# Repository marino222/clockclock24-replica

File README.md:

# ClockClock 24 Replica

This project is a hardware and software replica of the kinetic art piece "ClockClock 24" by *Humans Since 1982*, inspired by and building upon the work of [Vallasc](https://github.com/Vallasc/clockclock24-replica) with several hardware modifications and improvements. The clock features 24 double-shaft stepper motors arranged in an 8x3 matrix, with motors grouped in sets of three on custom PCBs, of which there are eight in total. Each board is controlled by a Raspberry Pi Pico microcontroller acting as a slave, while all slave boards communicate with a central ESP32 master via the I2C protocol. The ESP32 also provides a web interface for remote control and configuration.

---

## Table of Contents

1. [Repository Structure](#repository-structure)
2. [Hardware](#hardware)
    1. [Electronics](#electronics)
        1. [Motors](#motors)
        2. [Motor Drivers](#motor-drivers)
        3. [Microcontrollers](#microcontrollers)
        4. [PCB](#pcbs)
        5. [Power Supply](#power-supply)
    2. [Mechanics](#mechanics)
        1. [Clock hands](#clock-hands)
        2. [Fixation brackets](#fixation-brackets)
        3. [Front panel](#front-panel)
    3. [BOM](#bom)
3. [Software](#software)
    1. [Master](#master)
    2. [Slave](#slave)
    3. [Web Interface](#web-interface)
4. [Credits](#credits)

---

## Repository Structure

```
ClockClock 24 Replica/
├── 3D files/
│   ├── final/
│   └── test/
├── docs/
│   ├── datasheets/
│   └── images/
├── firmware/
│   ├── arduino/
│   │   ├── AdvancedBoardTest/
│   │   ├── BoardTest/
|   |   ├── SerialBoardTest/
│   │   └── SpeedoDriveTest/
│   ├── platformio/
│   │   ├── master/
│   │   └── slave/
│   └── README.md
├── pcb/
│   ├── Clock PCB/
│   └── Motor Driver/
└── README.md
```

---

## Hardware

### Electronics

#### Motors
To drive the clock hands, the BKA30D-R5 (equivalent to VID28-05) stepper motors were chosen. They have a total of 4 coils, allowing for two concentric drive shafts which makes them perfect for this application. These motors were originally designed for dashboard applications in the automotive industry. There are a number of other options with concentric shafts, but this one seemed to be most suitable as other similar projects also used it. Furthermore, it is cheaply available (around 4$ on Aliexpress) and draws little current.

<p align="center">
    
    <br><em>BKA30D-R5 stepper motor</em>
</p>

The BKA30D-R5 allows for microstepping up to 1/12 degrees per microstep, which is ideal to achieve smooth movement of the clock hands. See datasheet for more details: [BKA30D-R5 Datasheet](docs/datasheets/BKA30D-xx_datasheet.pdf).

*Note: As standard, this motor comes with mechanical endstops. On Aliexpress there are some vendors that sell it without endstops, otherwise you will need to cut off the endstops yourself.*

---

#### Motor Drivers
The steppers could in theory be driven directly from the microcontroller. However, the GPIO pins are limited and it is usually best practice to use a dedicated motor driver. For this reason, the VID6606 motor driver was chosen. It is specifically designed for the BKA30D-R5 (VID28-05) motor. One VID6606 can drive 4 motors (8 coils) in total. Per motor, it only needs two inputs: `f(SCX)` and `DIR`. As standard, this controller has built-in microstepping, which means with each rising edge of the SCX input the motor will perform one microstep in the direction specified by the DIR input.

The [VID6606 Datasheet](docs/datasheets/VID6606_datasheet.pdf) specifically recommends the use of smoothing capacitors to reduce electrical noise. Therefore, this [Motor-Controller-PCB from Hackaday](https://hackaday.io/project/187630-stepper-driver-for-dashpanel-instruments) was used. I didn't make any changes to it because it was already tested by [doctek](https://hackaday.io/doctek). Thus, it is designed to be used as a breakout board on the custom Clock PCB.

<p align="center"><em>Rendered image of the motor driver PCB</em></p>

During testing, the steppers were quite noisy. I first suspected the motor drivers and tried some alternatives (DRV8834, TMC2208), but that didn't help much, so I stayed with the VID6606. 

The real cause turned out to be mechanical play in the motor shafts. I also noticed the noise only appears at certain speeds, at full speed it mostly goes away. So adjusting the acceleration profile in software might help. For now I decided to leave the mechanical play as-is, since adding a bearing would be quite complex.

---

#### Microcontrollers
An ESP32 was chosen to run the master code, while multiple Raspberry Pi Picos are used as slave controllers. The ESP32 sends all the commands via I2C protocol to the slave boards. The main reason for this choice is that almost the same controllers were used in the reference project ([Vallasc/clockclock24-replica](https://github.com/Vallasc/clockclock24-replica)). Since I want to copy the software as closely as possible, I stuck with the same controllers. They are also widely available for a reasonable price and are easy to work with.

<p align="center"><em>Raspberry Pi Pico (left) and ESP32 (right)</em></p>

---

#### PCB
For the project, a custom Clock PCB was designed to hold three BKA30D-R5 motors, which is the maximum number of motors that can be driven by one Raspberry Pi Pico regarding available GPIO pins. In total, there are eight of these PCBs, resulting in an 8x3 matrix of 24 motors. Each Clock PCB has two VID6606 motor driver breakout boards, of which one output is unused.

As a design choice, the PCB uses header pins to connect the motor drivers and the microcontroller. This makes it easy to replace components in case they break. While testing, this happened multiple times. Since the motor controllers were directly soldered onto the PCB in the beginning, I ended up throwing away the whole PCB each time a motor driver broke. The header pins solve this problem. As a bonus, the Picos can be switched out easily. This proved useful to quickly run a test program by replacing the "normal" slave controller with a test controller running different firmware.

<p align="center"><em>Rendered image of the Clock PCB. See PCB directory for more info</em></p>

<p align="center"><em>Assembled Clock PCB</em></p>

---

#### Power Supply
All the PCBs are connected by a JST-XH 4-pin connector in a daisy chain. Two wires are used for power (5V and ground) and two wires are used for I2C communication (SDA and SCL). In theory, it should be possible to power all eight PCBs from one Raspberry Pi Pico connected to a power supply via USB-C. However, in reality this didnt work (see below).

#### Power Consumption Table

| Device                | Normal Current (mA) | Peak Current (mA) | Quantity | Total Normal (mA) | Total Peak (mA) |
|-----------------------|---------------------|-------------------|----------|-------------------|-----------------|
| Raspberry Pi Pico     | 50                  | 100               | 8        | 400               | 800             |
| Stepper Motor         | 20                  | 20                | 24       | 480               | 480             |
| ESP32                 | 260                 | 700               | 1        | 260               | 700             |
| **Total**             |                     |                   |          | **1140**          | **1980**        |

This table shows the estimated current draw for each device during normal use and at peak. The totals are for 8 Raspberry Pi Picos, 24 stepper motors, and 1 ESP32.

A Raspberry Pi Pico can provide up to 2 A via the VBUS pin when powered over USB-C, which should be enough even at peak load.

In practice I ran into power problems. When all motors start up at the same time, they draw a lot of current and the Pico's supply couldn't keep up, causing the ESP32 or some Picos to randomly shut down. To fix this, each PCB has an extra 2-pin JST power input. I disconnected the +5V lines on the JST-XH 4-pin connectors (GND and I2C stay connected) and wired the 2-pin terminals with 18 AWG wire and WAGO clamps to a separate supply.

The worst-case current draw is around 4 A, so I chose a 5 V / 6 A (30 W) PSU from [Amazon](https://www.amazon.de/dp/B0FY6691ZL), which gives a 2 A safety margin. It connects via a standard barrel jack that came with the PSU.

<p align="center"><em>Image of the connected PCBs</em></p>

### Mechanics

All mechanical parts are modeled in CAD. See the [3D files README](3D%20files/README.md) for the full assembly and a list of all printable parts.

#### Wooden Frame & Front panel

For the front panel I wanted a clean matte white look. After exploring several options (PVC, painted MDF, Corian), I found [expresszuschnitt.de](https://expresszuschnitt.de/) where you can order custom laser-cut materials. I ordered some samples and went with matte white acrylic (PERSPEX® Frost). The quality is excellent and the finish looks great. The front panel is bonded to the wooden frame with 3M VHB tape.

The frame itself is made from four wooden beams (see [BOM](#bom) for dimensions), connected at the corners by 3D-printed brackets that are screwed onto the beams.

<p align="center"><em>Wooden frame with acrylic front panel</em></p>

To give the clock a picture-frame look, I added medium oak ledges glued onto the main frame with mitered corners. Cutting accurate miters with basic tools was tricky, but after some sanding and oiling the result looks quite nice.

<p align="center"><em>Gluing the outer oak frame</em></p>

<p align="center"><em>Finished outer frame</em></p>

---

#### 2×3 Clock Arrays

The motors are grouped into 2×3 arrays. Each array consists of two PCBs connected by PCB mounts. Screw spacers raise the PCBs to the correct depth so the clock hands sit at the right position on the front. Everything is held together with M3 hex screws and threaded inserts.

<p align="center"><em>Exploded view (left) and front view (right) of a 2×3 clock array</em></p>

The arrays are aligned with the holes in the front panel using the [`mounting_aid.stl`](3D%20files/README.md) and then screwed to the wooden frame. The PSU barrel jack is clamped to the bottom of the frame with a 3D-printed bracket. A small cutout in the outer frame lets the power cable pass through.

<p align="center"><em>Clock arrays mounted to the frame</em></p>

---

#### Clamps

After mounting everything, I noticed a visible air gap between the 3D-printed PCB mounts and the front plate. This comes from slightly bent 3D-printed parts. The front panel also has quite a bit of flex.

<p align="center"><em>Gap between clock arrays and front panel</em></p>

To fix this, I designed a clamp to press the PCB holders onto the front plate. I tried different solutions, but none gave satisfying results. In the end, I settled on 3D-printed clamps that are screwed onto the main frame and use a spring section to press the PCB holders against the front plate.

<p align="center"><em>Section view of clamps</em></p>

Because of build-volume restrictions on my 3D printer, each clamp consists of multiple parts that are screwed together. As a result, and because the 3D-printed springs are quite strong, the clamp bends slightly. This can be seen in the image below. The bending causes the clamp to sit slightly higher than the outer frame. As a result, when the clock is mounted on a wall, the outer frame is not fully flush because the clamps push the clock outward. I decided to treat this as a design feature: it protects the rest of the clock, and the gap between the frame and the wall allows a bit of airflow, which helps cool the microcontrollers.

<p align="center"><em>Assembled clock with clamps</em></p>

---
### BOM

| Component | Description | Quantity | Source | Link |
|-----------|-------------|----------|--------|------|
| Clock PCB | Custom PCB holding 3 motors and a Raspberry Pi Pico. See PCB directory for the electronic BOM | 8 | JLCPCB, parts from AliExpress | [PCB README](pcb/Clock%20PCB/README.md) |
| PCB Mount (3D printed) | Mounts two PCBs together into one 2×3 array. 3 pieces per array | 9 | Self-printed | [3D files README](3D%20files/README.md) |
| PCB Mount Bottom (3D printed) | Same as PCB Mount but with corrected hole positions for the bottom PCB | 3 | Self-printed | [3D files README](3D%20files/README.md) |
| Mounting Bracket (3D printed) | Connects a 2×3 clock array to the wooden frame | 6 | Self-printed | [3D files README](3D%20files/README.md) |
| PSU Bracket (3D printed) | Clamps the PSU barrel jack to the wooden frame | 1 | Self-printed | [3D files README](3D%20files/README.md) |
| Frame Connector (3D printed) | Connects the outer frame corners. Parts are mirrored for each corner | 4 | Self-printed | [3D files README](3D%20files/README.md) |
| Screw Spacer (3D printed) | Raises PCBs slightly off the mounting brackets | 80 | Self-printed | [3D files README](3D%20files/README.md) |
| Lower Hand (3D printed) | Hour clock hand | 24 | Self-printed | [3D files README](3D%20files/README.md) |
| Upper Hand (3D printed) | Minute clock hand | 24 | Self-printed | [3D files README](3D%20files/README.md) |
| Wall Mount (3D printed) | Wall mounting part | 2 | Self-printed | [3D files README](3D%20files/README.md) |
| Outer Clamp (3D printed) | Outer clamp part | 5 | Self-printed | [3D files README](3D%20files/README.md) |
| Middle Clamp (3D printed) | Middle clamp part | 3 | Self-printed | [3D files README](3D%20files/README.md) |
| Y-Clamp (3D printed) | Y-clamp part | 1 | Self-printed | [3D files README](3D%20files/README.md) |
| Leaf Spring (3D printed) | Spring element used in the clamp assembly | 9 | Self-printed | [3D files README](3D%20files/README.md) |
| Edge Clamp (3D printed) | Edge clamp part for the right and left sides | 2 | Self-printed | [3D files README](3D%20files/README.md) |
| ESP32 mount (3D printed) | Mounting part for the ESP32 microcontroller | 1 | Self-printed | [3D files README](3D%20files/README.md) |
| Acrylic Front Panel | PERSPEX® Frost matte white acrylic, 900×400×5 mm | 1 | Imported from Germany | [expresszuschnitt.de](https://expresszuschnitt.de/) |
| Main Frame Long | 20×45×900 mm wood beam | 2 | Hardware store | [Jumbo](https://www.jumbo.ch/de/bauen-renovieren/holz/leisten-staebe/rechteckleisten/oecoplan-dachlatte-gehobelt-20-x-45mm--1m/p/4974449) |
| Main Frame Short | 20×45×400 mm wood beam | 2 | Hardware store | [Jumbo](https://www.jumbo.ch/de/bauen-renovieren/holz/leisten-staebe/rechteckleisten/oecoplan-dachlatte-gehobelt-20-x-45mm--1m/p/4974449) |
| Outer Frame Long | 8×40×920 mm oak ledge | 2 | Hardware store | [Jumbo](https://www.jumbo.ch/de/bauen-renovieren/holz/leisten-staebe/rechteckleisten/rechteckleiste-eiche-8x40-mm-1-m/p/4974225) |
| Outer Frame Short | 8×40×420 mm oak ledge | 2 | Hardware store | [Jumbo](https://www.jumbo.ch/de/bauen-renovieren/holz/leisten-staebe/rechteckleisten/rechteckleiste-eiche-8x40-mm-1-m/p/4974225) |
| Power Supply | 5 V / 6 A (30 W) PSU | 1 | Amazon | [Amazon](https://www.amazon.de/dp/B0FY6691ZL) |
| Power Wire | 18 AWG | ~3 m | AliExpress | |
| WAGO Clamps | Model 221-413 (3-conductor) | 14 | AliExpress | |
| 3M VHB Tape | 19 mm width | ~1 m | Hardware store | [3M Switzerland](https://www.3mschweiz.ch/3M/de_CH/p/c/klebebander/b/vhb/) |
| Countersunk Wood Screw | 4×16 mm | 24 | Hardware store | [Jumbo](https://www.jumbo.ch/de/maschinen-werkstatt/kleineisenwaren/schrauben/holzschrauben/ayce-senkkopf-universalholzschraube--4--16-mm/p/6932501) |
| Hex Screw | M3×8 mm | 96 | AliExpress | |
| Threaded Insert | M3×4×4 mm (for 3D-printed parts) | 96 | AliExpress | |

---

## Software

### Master

The master firmware runs on an ESP32 microcontroller and acts as the central brain of the clock. Its main responsibilities include:

- **Time Synchronization**: Automatically connects to WiFi to retrieve the current time, ensuring the clock is always accurate and handles time zones and daylight saving time seamlessly.
- **Clock Logic**: Orchestrates the movements of all clock hands, deciding exactly what positions they need to be in to display the time or play animations.
- **Communication**: Sends synchronized instructions to all eight slave boards so the 24 motors move perfectly together.
- **Web Server**: Hosts a web interface that allows you to configure and control the clock from any device.

The master code is built using PlatformIO with the Arduino framework.

### Slave

The slave firmware runs on each of the eight Raspberry Pi Pico microcontrollers, with each board responsible for controlling three BKA30D-R5 stepper motors (six individual clock hands). Key features include:

- **I2C Communication**: Listens for commands from the ESP32 master via I2C protocol
- **Motor Control**: Uses the AccelStepper library to provide smooth, accelerated motor movements with precise positioning
- **Automatic Addressing**: Determines its I2C address automatically based on DIP switch configuration (see below)

Each slave board operates independently once it receives position commands from the master, managing the acceleration profiles and step timing for its three motors in parallel.

Each slave board (Raspberry Pi Pico) determines its I2C address automatically based on four DIP switch pins (ADDR_1 through ADDR_4) defined in [`board_config.h`](firmware/platformio/slave/include/board_config.h). The address is calculated in [`board.cpp`](firmware/platformio/slave/src/board.cpp) by reading the state of these pins, which use INPUT_PULLUP logic. When a DIP switch is ON (connected to ground), it represents a binary 1. When OFF (open/floating), it represents a binary 0.

The master controller sends commands to each board sequentially as seen in [`clock_manger.cpp`](firmware/platformio/master/src/clock_manger.cpp), where I2C address 15 corresponds to the rightmost board. The first address is 0x08, because in the I2C protocol 0x01 to 0x07 are reserved.

#### Board Address Configuration (Left to Right)

| I2C Address | Binary | DIP 1 | DIP 2 | DIP 3 | DIP 4|
|-------------------|-------------|--------|----------------|--------------|--------------|
| 8  | 1000 | 1 | 0 | 0 | 0 |
| 9  | 1001 | 1 | 0 | 0 | 1 |
| 10 | 1010 | 1 | 0 | 1 | 0 |
| 11 | 1011 | 1 | 0 | 1 | 1 |
| 12 | 1100 | 1 | 1 | 0 | 0 |
| 13 | 1101 | 1 | 1 | 0 | 1 |
| 14 | 1110 | 1 | 1 | 1 | 0 |
| 15 | 1111 | 1 | 1 | 1 | 1 |

### Web Interface

The web interface is hosted directly on the ESP32 and provides an intuitive control panel for the ClockClock 24. To access it, simply connect to the same WiFi network as the ESP32 and navigate to its IP address in your browser. 

The UI provides the following features:
- **Live Preview**: View a real-time digital representation of what the physical clock is currently displaying.
- **Mode & Animation Selection**: Easily switch between the normal time display, various choreographies, or run test animations.
- **Sleep Time Configuration**: Define specific days and hours when the clock should stop moving to save power and reduce noise.
- **Wireless Configuration**: Seamlessly switch between the clock's own Hotspot mode or connect it to your home WiFi network.
- **Firmware Update**: Perform Over-The-Air (OTA) firmware updates directly from your browser.

The web interface is built using standard HTML, CSS, and JavaScript. Because the ESP32 has limited storage, a custom Node.js script is used to compress the web files. Before building the firmware, running `npm run minimize` minifies the UI files and converts them into a single, optimized C++ header file, which is then flashed onto the microcontroller.

For more technical details about the firmware, see the [firmware README](firmware/README.md).

### Clock Modes

The clock can operate in three distinct modes, which can be selected via the web interface:
- **OFF**: All clock hands move to a resting position (pointing straight down) and remain stationary.
- **LAZY**: A minimalist mode where the clock hands take the shortest, most direct path to the new time every minute, without any complex choreographies.
- **ANIMATED**: Every minute, the clock performs a choreography before settling on the new time. You can choose a specific animation or use the **Cycle** mode.

#### Cycle Mode & Randomness
When the **Cycle** animation is selected, the clock rotates through the available choreographies instead of playing the same one every minute. You have two options for how it cycles:
- **SEQ (Sequential)**: Plays the animations in a fixed order, cycling to the next one every minute.
- **RAND (Random)**: Plays a "random" animation each minute. Interestingly, this randomness is deterministic and based on the current time (a hash of the current minute of the day). This means the clock will always play the exact same animation, as the Web Interface.

### Animations

| Description      | Animation |
| ----------- | ----------- |
| Chaos |  |
| Waves |  |
| Circle |  |
| Spiral |  |
| Loom |  |
| Star |  |

## Credits

### Design — Humans Since 1982

**ClockClock 24 is an original kinetic art piece created by [Humans Since 1982](https://www.humanssince1982.com/).** All design rights, intellectual property, and artistic authorship of the ClockClock concept belong exclusively to them. This project is a non-commercial personal replica built out of admiration for their work. I make no claim to the design, the concept, or any related intellectual property.u are considering a similar project, please be aware of this and respect their rights.

---

### Reference Implementation — Vallasc

The firmware and PCB design of this project are largely based on the work of [Vallasc](https://github.com/Vallasc/clockclock24-replica). His open-source replica served as the primary reference for the software architecture, I2C communication protocol, clock logic, and overall system design. Without his work this project would have taken significantly longer to build.

---

### Motor Driver PCB — doctek

The motor driver breakout board design is taken from the [Stepper Driver for Dashpanel Instruments](https://hackaday.io/project/187630-stepper-driver-for-dashpanel-instruments) project by [doctek](https://hackaday.io/doctek) on Hackaday.io. The board was used without modifications. The `SpeedoDriveTest.ino` test sketch is also taken from that project.

---

### This Project

This repository is released under the [GNU General Public License v3.0](LICENSE). You are free to use, modify, and distribute it under the same terms, but **the design concept of ClockClock 24 remains the exclusive property of Humans Since 1982** and this license does not grant any rights to it.

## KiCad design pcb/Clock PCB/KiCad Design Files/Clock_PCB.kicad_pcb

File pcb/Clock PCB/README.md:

# Clock PCB — Main Board for ClockClock 24 Replica

This folder contains the design files, manufacturing resources, and assembly instructions for the Clock PCB used in the ClockClock 24 Replica project. The Clock PCB hosts three stepper motors, a Raspberry Pi Pico microcontroller, and connectors for two Motor Driver modules.

---

## Folder Contents

- **KiCad Design Files:** Schematic and layout for the Clock PCB.
- **Manufacturing Folder:**
  - Gerber files (ZIP) for PCB fabrication

---

## Manufacturing

1. **PCB Fabrication:**
   - Order the PCB from [JLCPCB](https://jlcpcb.com/) or a similar service.
   - Upload the Gerber ZIP file from the `Manufacturing` folder during the order process.

3. **Manual Assembly:**
    - Solder all the components manually

---

## Bill of Materials (BOM)

This BOM lists only the components that need to be soldered onto the Clock PCB. The full BOM for the final assembly is provided in [the main project README](../../README.md).

| Quantity | Reference      | Value                 | Footprint | Description               |
|----------|----------------|-----------------------|-----------|---------------------------|
| 3        | M1, M2, M3     | BKA30D-R5             | -         | Stepper Motor             |
| 2        | J1, J2         | JST-PH-4pin           | P2.0mm    | 4-pin JST PH, 90° angle   |
| 2        | -              | 20 pin female         | P2.54mm   |  20 Pin socket            |
| 2        | -              | 6 pin female header   | P2.54mm   | 6 Pin socket              |
| 1        | -              | 5 pin female header   | P2.54mm   | 5 Pin socket              |
| 1        | -              | 8 pin female header   | P2.54mm   | 8Pin socket               |
| 1        | SW1            | 4 bit                 | P2.54mm   | 4-bit DIP switch          |
| 1        | J3 (optional)  | Power connector       | P5.08mm   | Optional power connector  |

---

## Images

### Assembled Clock PCB Example
<p align="center">
  
  <br><em>Assembled Clock PCB</em>
</p>

### PCB Schematics
<p align="center">
  
  <br><em>Clock PCB Schematic</em>
</p>

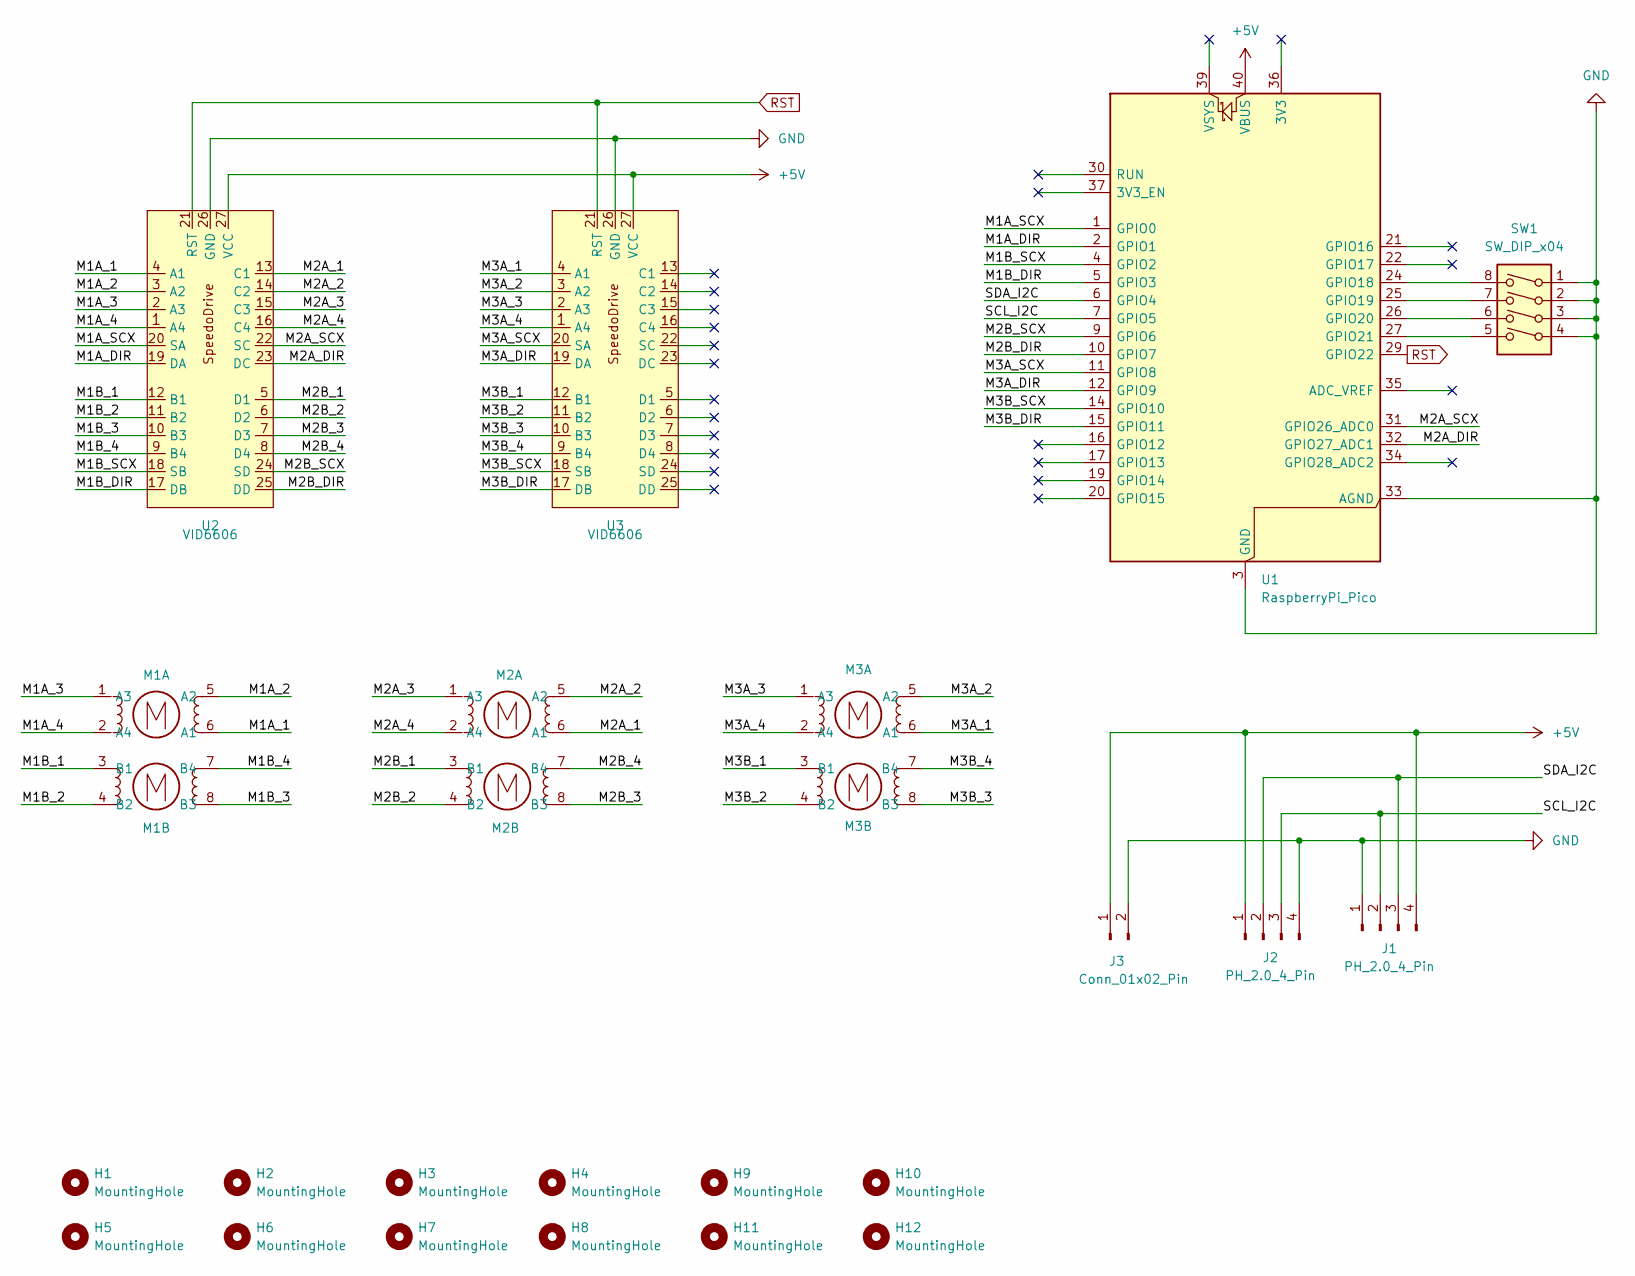
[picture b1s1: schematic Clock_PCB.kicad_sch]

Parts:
H1, H2, H3, H4, H5, H6, H7, H8, H9, H10, H11, H12: MountingHole; MountingHole_3.2mm_M3
J1, J2: PH_2.0_4_Pin; JST_PH_S4B-PH-K_1x04_P2.00mm_Horizontal
J3: Conn_01x02_Pin; TerminalBlock_Phoenix_MKDS-1,5-2-5.08_1x02_P5.08mm_Horizont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
M1, M2, M3: BKA30D-R5
SW1: SW_DIP_x04; SW_DIP_SPSTx04_Slide_9.78x12.34mm_W7.62mm_P2.54mm
U1: RaspberryPi_Pico; RaspberryPi_Pico_Common_THT_Header
U2, U3: VID6606; SpeedoDrive

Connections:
+5V: J1.4, J2.1, J3.1, U1.40 (VBUS), U2.27 (VCC), U3.27 (VCC)
/M1A_1: M1.6 (A1), U2.4 (A1)
/M1A_2: M1.5 (A2), U2.3 (A2)
/M1A_3: M1.1 (A3), U2.2 (A3)
/M1A_4: M1.2 (A4), U2.1 (A4)
/M1A_DIR: U1.2 (GPIO1), U2.19 (DA)
/M1A_SCX: U1.1 (GPIO0), U2.20 (SA)
/M1B_1: M1.3 (B1), U2.12 (B1)
/M1B_2: M1.4 (B2), U2.11 (B2)
/M1B_3: M1.8 (B3), U2.10 (B3)
/M1B_4: M1.7 (B4), U2.9 (B4)
/M1B_DIR: U1.5 (GPIO3), U2.17 (DB)
/M1B_SCX: U1.4 (GPIO2), U2.18 (SB)
/M2A_1: M2.6 (A1), U2.13 (C1)
/M2A_2: M2.5 (A2), U2.14 (C2)
/M2A_3: M2.1 (A3), U2.15 (C3)
/M2A_4: M2.2 (A4), U2.16 (C4)
/M2A_DIR: U1.32 (GPIO27_ADC1), U2.23 (DC)
/M2A_SCX: U1.31 (GPIO26_ADC0), U2.22 (SC)
/M2B_1: M2.3 (B1), U2.5 (D1)
/M2B_2: M2.4 (B2), U2.6 (D2)
/M2B_3: M2.8 (B3), U2.7 (D3)
/M2B_4: M2.7 (B4), U2.8 (D4)
/M2B_DIR: U1.10 (GPIO7), U2.25 (DD)
/M2B_SCX: U1.9 (GPIO6), U2.24 (SD)
/M3A_1: M3.6 (A1), U3.4 (A1)
/M3A_2: M3.5 (A2), U3.3 (A2)
/M3A_3: M3.1 (A3), U3.2 (A3)
/M3A_4: M3.2 (A4), U3.1 (A4)
/M3A_DIR: U1.12 (GPIO9), U3.19 (DA)
/M3A_SCX: U1.11 (GPIO8), U3.20 (SA)
/M3B_1: M3.3 (B1), U3.12 (B1)
/M3B_2: M3.4 (B2), U3.11 (B2)
/M3B_3: M3.8 (B3), U3.10 (B3)
/M3B_4: M3.7 (B4), U3.9 (B4)
/M3B_DIR: U1.15 (GPIO11), U3.17 (DB)
/M3B_SCX: U1.14 (GPIO10), U3.18 (SB)
/SCL_I2C: J1.2, J2.3, U1.7 (GPIO5)
/SDA_I2C: J1.3, J2.2, U1.6 (GPIO4)
GND: J1.1, J2.4, J3.2, SW1.1, SW1.2, SW1.3, SW1.4, U1.3 (GND), U1.8 (GND), U1.13 (GND), U1.18 (GND), U1.23 (GND), U1.28 (GND), U1.33 (AGND), U1.38 (GND), U2.26 (GND), U3.26 (GND)
unnamed: SW1.8, U1.24 (GPIO18)
unnamed: SW1.7, U1.25 (GPIO19)
unnamed: SW1.6, U1.26 (GPIO20)
unnamed: SW1.5, U1.27 (GPIO21)
RST: U1.29 (GPIO22), U2.21 (RST), U3.21 (RST)

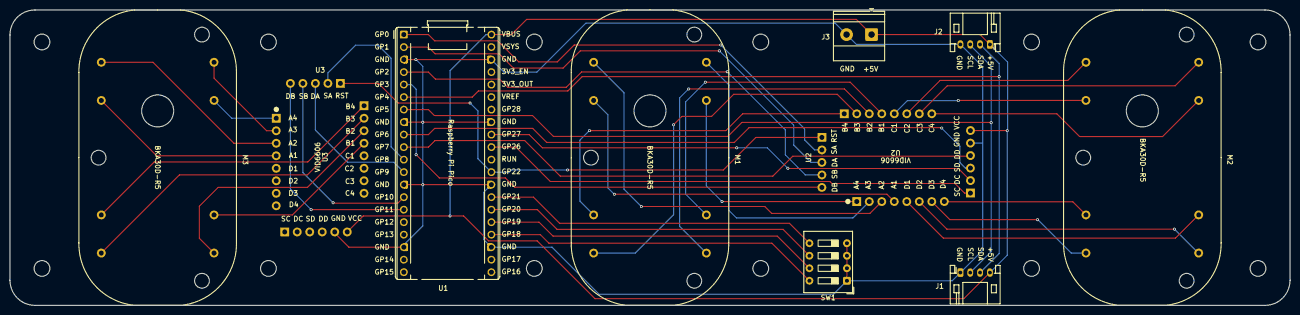
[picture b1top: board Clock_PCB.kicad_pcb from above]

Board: 2 copper layers, 260.0 x 60.0 mm, 22 parts (0 on the bottom side), 45 nets.

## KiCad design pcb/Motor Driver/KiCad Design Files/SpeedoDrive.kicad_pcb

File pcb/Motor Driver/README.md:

# Motor Driver PCB — VID6606 Breakout

This folder contains the design files, manufacturing resources, and assembly instructions for the Motor Driver PCB used in the ClockClock 24 Replica project. This board is a compact breakout for the VID6606 stepper driver IC, designed to be easily replaceable and compatible with the main Clock PCB.

---

## Folder Contents

- **KiCad Design Files:** Schematic and layout for the Motor Driver PCB.
- **Manufacturing Folder:**
  - Gerber files (ZIP) for PCB fabrication
  - [SpeedoDrive_BOM_SMD.csv](Manufacturing/SpeedoDrive_BOM_SMD.csv): Machine-readable BOM for SMD assembly

---

## Manufacturing 

1. **PCB Fabrication:**
   - The PCB was ordered from [JLCPCB](https://jlcpcb.com/)
   - Upload the Gerber ZIP file from the `Manufacturing` folder when placing your order

2. **SMD Assembly:**
    - The automatic assembly of SMD components (excluding the VID6606) was also ordered from JLCPCB.
    - During the order proces you will be prompted to upload a BOM file, to automatically populate the pcb. Use the CSV file in the `Manufacturing` folder for this purpose
    - Of course, the SMD Components can also be soldered manually if preferred.

3. **Manual Assembly:**
    - Since the VID6606 chip and the pin headers cannot be automatically assembled, these components must be soldered manually after receiving the PCB.

---

## Bill of Materials (BOM)

This BOM lists all components required to assemble one Motor Driver board.

| Quantity | Reference   | Value   | Footprint | Description           |
|----------|-------------|---------|-----------|-----------------------|
| 1        | U1          | VID6606 | —         | Stepper Driver IC     |
| 2        | C1, C6      | 6.8 µF  | 0805      | Ceramic Capacitor     |
| 2        | C2, C5      | 4.7 µF  | 0805      | Ceramic Capacitor     |
| 2        | C3, C4      | 100 nF  | 0603      | Ceramic Capacitor     |
| 9        | R1–R9       | 10 kΩ   | 0603      | Resistor              |
| 1        | J1          | Header 5P | 2.54 mm | Pin Header            |
| 1        | J2          | Header 8P | 2.54 mm | Pin Header            |
| 2        | J3, J4      | Header 6P | 2.54 mm | Pin Header            |

---

## Images

### Soldered PCB Example
Without Pin Headers
<p align="center">
  
  <br><em>Soldered Motor Driver PCB</em>
</p>

### PCB Schematics
<p align="center">
  
  <br><em>Motor Driver Schematic</em>
</p>

### Mechanical Pin Numbers
Below is an illustration of the mechanical pin numbers for the Speedo Drive PCB. This helps identify the physical pin layout and connections for assembly and troubleshooting. The pin numbering shown here was used to design the KiCad footprint for this board.

<p align="center">
  
  <br><em>Mechanical Pin Numbers for Speedo Drive PCB</em>
</p>

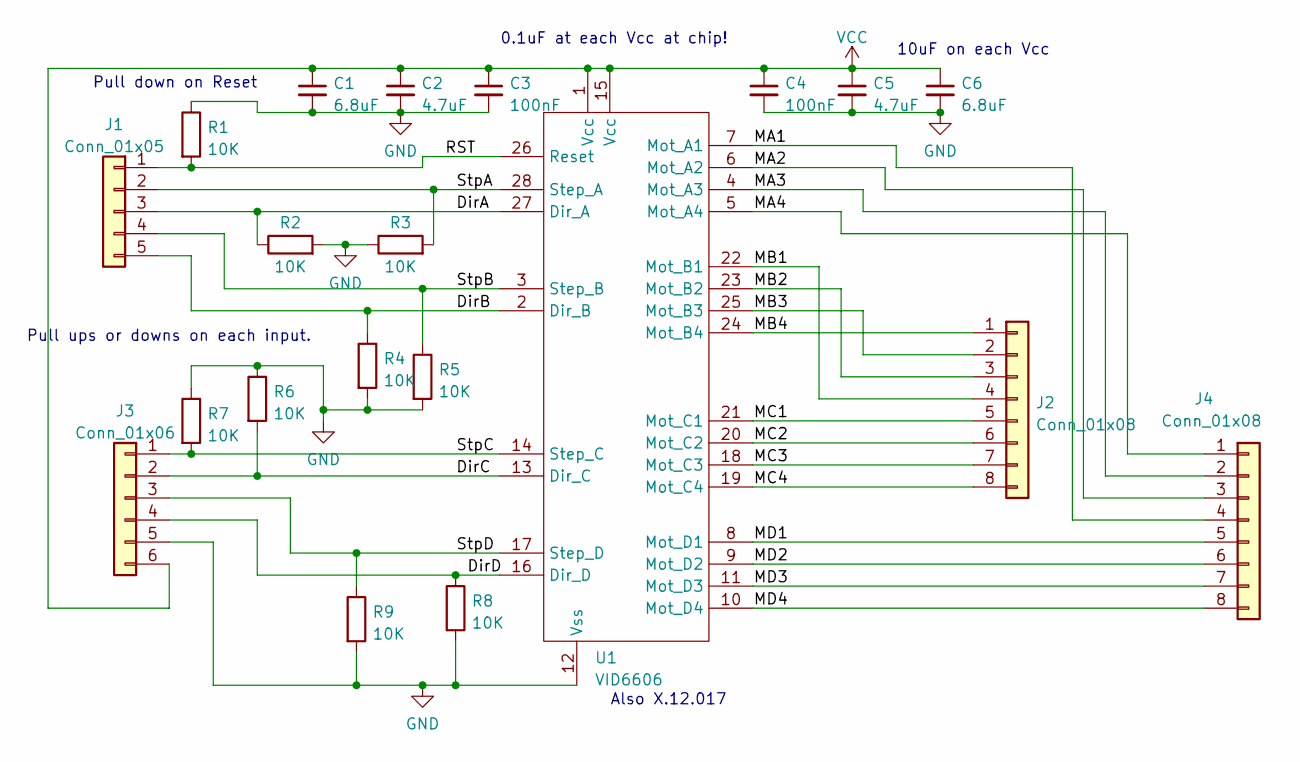
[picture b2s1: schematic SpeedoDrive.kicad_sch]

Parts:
C1, C6: 6.8uF; C_0805_2012MetricSQ; LCSC C5139488
C2, C5: 4.7uF; C_0805_2012MetricSQ; LCSC C1779
C3, C4: 100nF; C_0603_1608MetricSQ; LCSC C14663
J1: Conn_01x05; PinHeader_1x05_P2.54mm_Vertical
J2, J4: Conn_01x08; PinHeader_1x08_P2.54mm_Vertical
J3: Conn_01x06; PinHeader_1x06_P2.54mm_Vertical
R1, R2, R3, R4, R5, R6, R7, R8, R9: 10K; R_0603_1608MetricSQ; LCSC C25804
U1: VID6606; SOIC-28W_7.5x17.9mm_P1.27mm

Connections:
/DirA: J1.3, R2.1, U1.27 (Dir_A)
/DirB: J1.5, R4.1, U1.2 (Dir_B)
/DirC: J3.2, R6.2, U1.13 (Dir_C)
/DirD: J3.4, R8.1, U1.16 (Dir_D)
/MA1: J4.4, U1.7 (Mot_A1)
/MA2: J4.3, U1.6 (Mot_A2)
/MA3: J4.2, U1.4 (Mot_A3)
/MA4: J4.1, U1.5 (Mot_A4)
/MB1: J2.4, U1.22 (Mot_B1)
/MB2: J2.3, U1.23 (Mot_B2)
/MB3: J2.2, U1.25 (Mot_B3)
/MB4: J2.1, U1.24 (Mot_B4)
/MC1: J2.5, U1.21 (Mot_C1)
/MC2: J2.6, U1.20 (Mot_C2)
/MC3: J2.7, U1.18 (Mot_C3)
/MC4: J2.8, U1.19 (Mot_C4)
/MD1: J4.5, U1.8 (Mot_D1)
/MD2: J4.6, U1.9 (Mot_D2)
/MD3: J4.7, U1.11 (Mot_D3)
/MD4: J4.8, U1.10 (Mot_D4)
/RST: J1.1, R1.2, U1.26 (Reset)
/StpA: J1.2, R3.2, U1.28 (Step_A)
/StpB: J1.4, R5.1, U1.3 (Step_B)
/StpC: J3.1, R7.2, U1.14 (Step_C)
/StpD: J3.3, R9.1, U1.17 (Step_D)
GND: C1.2, C2.2, C3.2, C4.2, C5.2, C6.2, J3.5, R1.1, R2.2, R3.1, R4.2, R5.2, R6.1, R7.1, R8.2, R9.2, U1.12 (Vss)
VCC: C1.1, C2.1, C3.1, C4.1, C5.1, C6.1, J3.6, U1.1 (Vcc), U1.15 (Vcc)

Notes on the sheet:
0.1uF at each Vcc at chip!
Pull down on Reset
Also X.12.017
10uF on each Vcc
Pull ups or downs on each input.

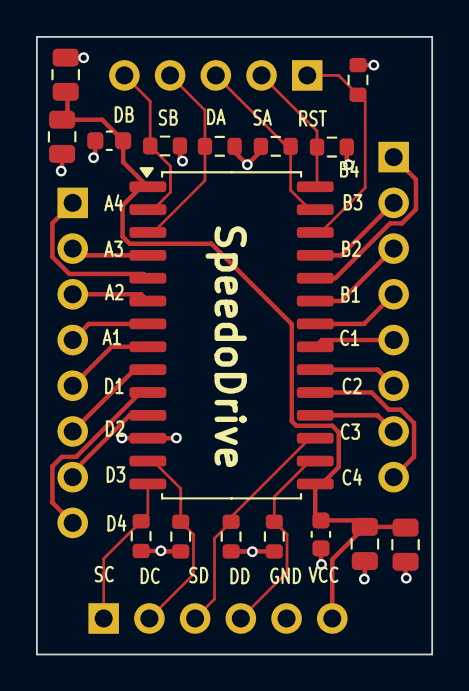
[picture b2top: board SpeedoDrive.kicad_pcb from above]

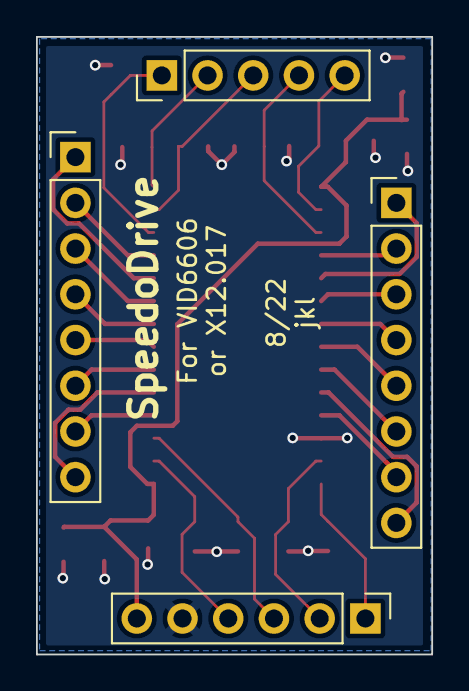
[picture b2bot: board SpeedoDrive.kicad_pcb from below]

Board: 2 copper layers, 22.0 x 34.3 mm, 20 parts (4 on the bottom side), 27 nets.

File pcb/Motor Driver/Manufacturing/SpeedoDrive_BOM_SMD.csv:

"Comment","Designator","Footprint","LCSC Part Number"
"6.8uF","C1,C6","0805","C5139488"
"4.7uF","C2,C5","0805","C1779"
"100nF","C3,C4","0603","C14663"
"10K","R1,R2,R3,R4,R5,R6,R7,R8,R9","0603","C25804"

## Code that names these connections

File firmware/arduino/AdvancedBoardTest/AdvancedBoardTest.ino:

/*
 * AdvancedBoardTest (ClockClock 24 Replica)
 *
 * Purpose
 * - Test any single stepper motor on the board by selecting it via a 4-bit DIP address (GPIO 18–21).
 * - While the address is valid and unchanged, the selected motor continuously:
 *     (1) rotates N full rotations forward
 *     (2) then rotates N full rotations backward
 *   repeating forever.
 * - If the address changes, the currently commanded motor is stopped (no further step pulses are issued)
 *   and control immediately switches to the newly addressed motor.
 * - If the address does not match any defined motor, all motors remain stopped.
 *
 * 4-bit address -> stepper mapping (exactly 6 unique addresses)
 * - Bit order: GPIO18 = b0 (LSB), GPIO19 = b1, GPIO20 = b2, GPIO21 = b3 (MSB)
 * - DIP read uses INPUT_PULLUP:
 *     switch ON (to GND)  => reads LOW  => bit = 1
 *     switch OFF (open)   => reads HIGH => bit = 0
 *
 *   Address (b1 b2 b3 b4)   Hex   Motor
 *   ---------------------   ---   -----
 *   0  0  0  0              0x0   A
 *   0  0  0  1              0x1   B
 *   0  0  1  0              0x2   C
 *   0  0  1  1              0x3   D
 *   0  1  0  0              0x4   E
 *   0  1  0  1              0x5   F
 *
 * GPIO usage summary
 * - Motor STEP/DIR pins:
 *     A: STEP=0  DIR=1
 *     B: STEP=2  DIR=7
 *     C: STEP=26 DIR=27
 *     D: STEP=6  DIR=3
 *     E: STEP=8  DIR=9
 *     F: STEP=10 DIR=11
 */

#include <Arduino.h>
#include <AccelStepper.h>

// Reuse the BoardTest notion of "one full rotation".
#define STEPS (360 * 12)

// Motion pattern constants
static const uint8_t N_ROTATIONS = 3;  // N (forward and backward); adjust as desired
static const long FORWARD_STEPS = (long)N_ROTATIONS * (long)STEPS;
static const long BACKWARD_STEPS = (long)N_ROTATIONS * (long)STEPS;

// DIP switch pins (4-bit binary address input)
static const uint8_t ADDR_B0_PIN = 18;
static const uint8_t ADDR_B1_PIN = 19;
static const uint8_t ADDR_B2_PIN = 20;
static const uint8_t ADDR_B3_PIN = 21;

#define A_STEP 0  // f(scx)
#define A_DIR 1   // CW/CCW
#define B_STEP 2  // f(scx)
#define B_DIR 7   // CW/CCW

#define C_STEP 26  // f(scx)
#define C_DIR 27   // CW/CCW
#define D_STEP 6   // f(scx)
#define D_DIR 3    // CW/CCW

#define E_STEP 8   // f(scx)
#define E_DIR 9    // CW/CCW
#define F_STEP 10  // f(scx)
#define F_DIR 11   // CW/CCW

#define RESET 22

// Stepper objects (exactly as in BoardTest.ino)
AccelStepper s_A(AccelStepper::DRIVER, A_STEP, A_DIR);
AccelStepper s_B(AccelStepper::DRIVER, B_STEP, B_DIR);
AccelStepper s_C(AccelStepper::DRIVER, C_STEP, C_DIR);
AccelStepper s_D(AccelStepper::DRIVER, D_STEP, D_DIR);
AccelStepper s_E(AccelStepper::DRIVER, E_STEP, E_DIR);
AccelStepper s_F(AccelStepper::DRIVER, F_STEP, F_DIR);

AccelStepper* motors[] = { &s_A, &s_B, &s_C, &s_D, &s_E, &s_F };
static const uint8_t NUM_MOTORS = sizeof(motors) / sizeof(motors[0]);

enum MotionPhase : uint8_t {
  PHASE_FORWARD = 0,
  PHASE_BACKWARD = 1,
};

static int8_t activeMotorIndex = -1;  // -1 means "none"
static uint8_t lastAddress = 0xFF;    // force initial update
static MotionPhase phase = PHASE_FORWARD;
static bool moveStarted = false;

static uint8_t readAddress4bit() {
  const uint8_t b0 = (digitalRead(ADDR_B0_PIN) == LOW) ? 1 : 0;
  const uint8_t b1 = (digitalRead(ADDR_B1_PIN) == LOW) ? 1 : 0;
  const uint8_t b2 = (digitalRead(ADDR_B2_PIN) == LOW) ? 1 : 0;
  const uint8_t b3 = (digitalRead(ADDR_B3_PIN) == LOW) ? 1 : 0;
  return (uint8_t)((b3 << 3) | (b2 << 2) | (b1 << 1) | b0);
}

static int8_t addressToMotorIndex(uint8_t address) {
  // Exactly 6 unique addresses are valid.
  switch (address) {
    case 0x0: return 0;  // A
    case 0x1: return 1;  // B
    case 0x2: return 2;  // C
    case 0x3: return 3;  // D
    case 0x4: return 4;  // E
    case 0x5: return 5;  // F
    default: return -1;
  }
}

static void stopAllMotors() {
  for (uint8_t i = 0; i < NUM_MOTORS; i++) {
    AccelStepper* m = motors[i];
    m->stop();
    m->moveTo(m->currentPosition());
    m->setSpeed(0);
  }
}

static void startSelectedMotorPattern(int8_t motorIndex) {
  if (motorIndex < 0 || motorIndex >= (int8_t)NUM_MOTORS) {
    return;
  }

  AccelStepper* m = motors[motorIndex];

  // Make the test deterministic whenever a motor is (re)selected.
  m->setCurrentPosition(0);

  phase = PHASE_FORWARD;
  moveStarted = false;
}

void setup() {
  Serial.begin(115200);
  Serial.println("ClockClock 24 replica advanced board test (DIP-addressed single motor)");

  pinMode(25, OUTPUT);
  digitalWrite(25, HIGH);

  // Reset motor controllers
  pinMode(RESET, OUTPUT);
  digitalWrite(RESET, HIGH);

  // DIP address pins
  pinMode(ADDR_B0_PIN, INPUT_PULLUP);
  pinMode(ADDR_B1_PIN, INPUT_PULLUP);
  pinMode(ADDR_B2_PIN, INPUT_PULLUP);
  pinMode(ADDR_B3_PIN, INPUT_PULLUP);

  // Set motor parameters (same as BoardTest.ino)
  for (uint8_t i = 0; i < NUM_MOTORS; i++) {
    motors[i]->setMaxSpeed(16000);
    motors[i]->setAcceleration(2000);
    motors[i]->setCurrentPosition(0);
  }

  stopAllMotors();
}

void loop() {
  const uint8_t address = readAddress4bit();

  // Address change: stop current motor and switch immediately.
  if (address != lastAddress) {
    lastAddress = address;

    stopAllMotors();

    activeMotorIndex = addressToMotorIndex(address);
    if (activeMotorIndex >= 0) {
      Serial.print("Selected motor ");
      Serial.print((char)('A' + activeMotorIndex));
      Serial.print(" (address 0x");
      Serial.print(address, HEX);
      Serial.println(")");

      startSelectedMotorPattern(activeMotorIndex);
    } else {
      Serial.print("Invalid address 0x");
      Serial.print(address, HEX);
      Serial.println(" -> all motors stopped");

      phase = PHASE_FORWARD;
      moveStarted = false;
    }
  }

  // If no valid motor is selected, keep everything stopped.
  if (activeMotorIndex < 0) {
    return;
  }

  AccelStepper* m = motors[activeMotorIndex];

  // Schedule a move when needed.
  if (!moveStarted) {
    const long delta = (phase == PHASE_FORWARD) ? FORWARD_STEPS : -BACKWARD_STEPS;
    m->move(delta);
    moveStarted = true;

    Serial.print("Motor ");
    Serial.print((char)('A' + activeMotorIndex));
    Serial.print(phase == PHASE_FORWARD ? " forward " : " backward ");
    Serial.println("segment");
  }

  // Non-blocking motion.
  m->run();

  // Segment complete -> flip phase and schedule next segment.
  if (moveStarted && m->distanceToGo() == 0) {
    if (phase == PHASE_FORWARD) {
      phase = PHASE_BACKWARD;
      moveStarted = false;
    } else {
      // Backward complete -> reset position and repeat forward.
      m->setCurrentPosition(0);
      phase = PHASE_FORWARD;
      moveStarted = false;
    }
  }
}

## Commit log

2025-12-20 Add README files for firmware and PCB design documentation
2025-12-20 Enhance firmware documentation and add Arduino test scripts for motor control
2025-12-20 Changed pcb\README
2025-12-21 Add README for 3D models directory
2025-12-21 Add .gitignore to exclude KiCad project files
2025-12-21 Added KiCad Design Files for Motor Driver
2025-12-21 Add STL files for clockclock24 lower and upper hands
2025-12-21 Changed 3D models\README
2025-12-21 Add BKA30D-xx stepper motor datasheet PDF
2025-12-21 Add reference to BKA30D-R5 datasheet in README
2025-12-21 Add README for Motor Driver PCB with manufacturing instructions and images
2025-12-21 Add BOM and Gerber files for SpeedoDrive Motor Driver
2025-12-21 Added schematics, and 3D-Model for Motor Controller PCB
2025-12-21 Replaced STl with STEP
2025-12-21 Revert "Replaced STl with STEP"
    This reverts commit a0bf36969092759c93fa24be8c9574c88c82bfb0.
2025-12-21 Update README to include PCB schematics image
2025-12-21 Refine README for PCB design files: enhance clarity and consistency in descriptions
2025-12-21 Added firmware source code for master and slave
2025-12-21 Update README files for firmware and Arduino scripts
2025-12-21 Improve comments in BoardTest.ino
2025-12-21 Changed firmware\README
2025-12-21 Add AdvancedBoardTest for stepper motor control using DIP address
2025-12-21 Add AdvancedBoardTest for testing stepper motors with DIP addressing
2025-12-21 Remove obsolete test scripts for stepper motor control
2025-12-21 Add speedo drive test setup image to documentation
2025-12-21 Changed file path
2025-12-21 Refactor SpeedoDriveTest for VID6606 compatibility and improve motor control logic
2025-12-22 Add VID6606 datasheet PDF for stepper motor driver
2025-12-23 Added datasheet for Raspberry Pi Pico
2025-12-23 Added electronics description to README.md
2025-12-23 Add new images for BKA30D, ESP32, motor driver, and Raspberry Pi Pico
2025-12-23 Changes on kicad files for Motor Driver
2025-12-23 Enhance README.md with detailed descriptions and images for BKA30D-R5 motors, VID6606 motor drivers, and power supply specifications
2025-12-23 Changed introduction to README.md
2025-12-23 Added KiCad design files for Clock PCB
2025-12-24 Add mechanical pin number illustration to Motor Driver README.md
2025-12-24 Clock PCB development
2025-12-25 KiCad PCB changes - PCB now finished, Design Review pending
2025-12-25 Added PCB schematics and 3d model
2025-12-25 Moved KiCad Files into folder
2025-12-26 Changes on Clock PCB
2025-12-26 Added Gerber Files for testing (not final)
2025-12-26 Update Clock PCB
2025-12-31 Update motor driver capacity in README
    Corrected the number of motors that can be driven by one VID6606 motor driver from two to four.
2026-01-07 Added rendered image of Clock PCB
2026-01-08 Refined Documentation
2026-01-08 Changed pdb/README.md
2026-02-14 Fixed the GPIO matching
2026-02-22 Added: - API endpoints for testing - http test script - Arduino SerialBoardTest script - documentation
2026-02-26 Moved arduino file
2026-02-28 Changes in SerialBoardTest
2026-02-28 Added new arduino testing script Documented motor driver test
2026-02-28 Clarified I2C address numbering in README.md
2026-02-28 Set binary addresses right
2026-02-28 Coorected pin numbers in board_config.h
2026-02-28 Switched motors a & b with c & d
2026-03-02 Added and moved 3d files
2026-03-22 Add I2C scanning functionality and update pin configurations in firmware
2026-04-12 Major update
2026-05-15 Added description about gap clamps Added new 3d files Added new images
2026-05-16 Added esp32_mount
2026-05-16 Added credits section
2026-05-16 Added details to Readme
2026-05-16 Implemented over-the-air updates Added updating page Changed web-url to "clock"
2026-05-16 Simplified testing - embedded testing function into firmware - create node js script to execute tests from terminal
2026-05-29 Fixed I2C communication issues
2026-05-29 Update README to remove getting started section
    Removed 'How to get started' section and adjusted related text.
2026-05-29 Implemented first draft for new animations: - new API endpoints - distinction between mode and animation - animations are still in progress
2026-05-31 Implemented circle animation Added button to test animation
2026-05-31 - Implemented JS web animations - Use same seed for "random" animation on firmware and web - made code more readable by separating inline css and js from html
2026-05-31 Refactor clock management and enhance web assets
    - Removed debug print statements in clock manager for cleaner code.
    - Added new functions for calculating angles in a circular layout for clock hands.
    - Implemented a new set_circle function to manage clock animations in three phases.
    - Updated web minimization script to inline CSS and JS files for better performance.
    - Adjusted attractor path in script.js to align with new clock grid dimensions.
2026-06-01 Implemented Spiral Animation in C++
2026-06-01 Implemented attract animation, however it is currently unstable
2026-06-03 Fixed circle animation in script.js
2026-06-03 Implemented Phase 1 of circle animation in C++: - hands form an attractor field in a circle shape - after a few seconds it goes back to displaying the time
2026-06-04 Fully implemented circle animation
2026-06-04 Implemented loom animation
2026-06-04 - Implemented Star animation - removed attract animation as it was unstable
2026-06-05 Added animation videos Revised Readme
2026-06-05 Added videos
2026-06-05 Update README to remove old asset links
    Removed outdated asset links from the README.
2026-06-06 Replaced mp4 with gif in Readme
2026-06-06 Changed size of animation gifs
2026-06-06 Updated Repository Structure in README
